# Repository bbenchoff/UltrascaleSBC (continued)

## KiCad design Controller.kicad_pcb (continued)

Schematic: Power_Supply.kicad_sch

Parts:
C42, C51, C53, C129, C130: 1uF; C_0402_1005Metric; MPN CL05A105KA5NQNC; LCSC C52923
C43, C44, C48, C49, C50, C219: 4.7uF; C_0402_1005Metric; MPN CL05A475MP5NRNC; LCSC C23733
C45, C46: 2.2uF; C_0402_1005Metric; MPN CL05A225KO5NQNC; LCSC C170151
C47, C52, C54, C55, C79, C88, C97: 100nF; C_0402_1005Metric; MPN CL05B104KO5NNNC; LCSC C1525
C58, C73: 10uF; C_0402_1005Metric; MPN CL05A106MP5NUNC; LCSC C315248
C59, C60, C61, C62, C63, C64, C65, C66, C67, C68, C69, C70, C71, C72, C74, C75, C80, C81, C82, C83, C84, C85, C89, C90, C91, C92, C93, C94, C98, C99, C100, C101, C217, C218: 22uF; C_0603_1608Metric; MPN CC0603MRX5R5BB226; LCSC C109448
C77, C78, C86, C87, C95, C96, C221: 22uF; C_0805_2012Metric; MPN CGA0805X5R226M250MT; LCSC C6119899
D1, D2: LED; LED_0603_1608Metric; MPN KT-0603G; LCSC C12624
IC1: TPS6508640RSKR; QFN40P800X800X100-65N-D; Mouser Part Number 595-TPS6508640RSKR
J2: Conn_01x03_Pin; JST_VH_B3PS-VH_1x03_P3.96mm_Horizontal; MPN B3PS-VH(LF)(SN); LCSC C131336
L1, L2, L3: 0.47µH; L_Chilisin_BWVS00505020; MPN SMNR5020-R47MT; LCSC C135279
L4, L6: 0.47µH; L_Vishay_IFSC-1515AH_4x4x1.8mm; MPN HTMD-4020-R47-M; LCSC C54321646
L5: 1µH; L_Bourns_SRP7028A_7.3x6.6mm; MPN SRP7028A-1R0M; LCSC C3223644
NT1, NT2, NT3: NetTie_2; NetTie-2_SMD_Pad0.5mm
Q1: BSS138; SOT-23; MPN BSS138; LCSC C7420339
R88, R89, R90, R91, R92, R93, R95, R96, R97, R98, R99, R100, R101: 10kΩ; R_0402_1005Metric; Tolerance 1%; MPN 0402WGF1002TCE; LCSC C25744
R198, R199, R200, R201, R202, R203: 2.2Ω; R_0402_1005Metric; Tolerance 1%; MPN RC0402FR-072R2L; LCSC C327251
R212: 2.2kΩ; R_0805_2012Metric; Tolerance 1%; MPN 0805W8F2201T5E; LCSC C17520
R213: 470Ω; R_0805_2012Metric; Tolerance 1%; MPN 0805W8F4700T5E; LCSC C17710
U23, U24, U25: CSD87381P; CSD87381P_TEX; MPN CSD87381P; LCSC C464808

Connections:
+0V6_VTT: C74.1, C75.1, C217.1, C218.1, IC1.47 (VTT), IC1.48 (VTTFB); also elsewhere on the board
+0V9_BUCK4: C64.1, C65.1, C66.1, C67.1, IC1.23 (FB4), L2.2
+0V85_VCCINT: C80.1, C81.1, C82.1, C83.1, C84.1, C85.1, IC1.2 (FBVOUT2), L4.1; also elsewhere on the board
+1V2_LDOA3: C50.1, IC1.49 (LDOA3)
+1V2_MGTAVTT: C69.1, C70.1, C71.1, C72.1, IC1.12 (FB3), L3.2; also elsewhere on the board
+1V2_VDDQ: C73.1, C98.1, C99.1, C100.1, C101.1, IC1.44 (FBVOUT6), IC1.46 (PVINVTT), L6.1; also elsewhere on the board
+1V5_LDOA2: C49.1, IC1.51 (LDOA2)
+1V8: C53.1, C59.1, C60.1, C61.1, C62.1, C219.1, IC1.18 (PVINSWB1_B2), IC1.22 (FB5), IC1.50 (PVINLDOA2_A3), L1.2; also elsewhere on the board
+1V8_MGTAVCCAUX: C54.1, IC1.17 (SWB1)
+1V8_SWB2: C55.1, IC1.19 (SWB2)
+2V5_VPP: C48.1, IC1.9 (LDOA1); also elsewhere on the board
+3V3: C51.1, C58.1, C63.1, C68.1, C89.1, C90.1, C91.1, C92.1, C93.1, C94.1, IC1.11 (PVIN3), IC1.21 (PVIN5), IC1.24 (PVIN4), IC1.29 (FBVOUT1), IC1.32 (PVINSWA1), L5.1, R213.2; also elsewhere on the board
+3V3_PMIC: C43.1, IC1.54 (LDO3P3), R88.2, R89.1, R90.1, R93.2, R95.2, R96.2, R97.2, R98.2
+3V3_PSIO: C52.1, IC1.31 (SWA1); also elsewhere on the board
+12V: C42.2, C77.1, C78.1, C86.1, C87.1, C95.1, C96.1, C129.2, C130.2, C221.1, IC1.55 (VSYS), J2.1, R212.2, U23.2 (VIN), U24.2 (VIN), U25.2 (VIN); also elsewhere on the board
/Power_Supply/+5_DRV: C44.1, C45.1, C46.1, IC1.8 (DRV5V_2_A1), IC1.38 (DRV5V_1_6), IC1.56 (LDO5P0), IC1.57 (V5ANA)
/Power_Supply/DRVH1: IC1.33 (DRVH1), R201.1
/Power_Supply/DRVH2: IC1.3 (DRVH2), R198.1
/Power_Supply/DRVH6: IC1.43 (DRVH6), R203.1
/Power_Supply/DRVL1: IC1.37 (DRVL1), R200.2
/Power_Supply/DRVL2: IC1.7 (DRVL2), R199.2
/Power_Supply/DRVL6: IC1.39 (DRVL6), R202.2
/Power_Supply/GPO1: IC1.16 (GPO1), IC1.62 (CTL4)
/Power_Supply/PGNDSNS1: IC1.36 (PGNDSNS1), NT2.2
/Power_Supply/PGNDSNS2: IC1.6 (PGNDSNS2), NT1.1
/Power_Supply/PGNDSNS6: IC1.40 (PGNDSNS6), NT3.1
/Power_Supply/SW1: C88.1, IC1.34 (SW1), L5.2, U23.5 (VSW)
/Power_Supply/SW2: C79.1, IC1.4 (SW2), L4.2, U24.5 (VSW)
/Power_Supply/SW6: C97.2, IC1.42 (SW6), L6.2, U25.5 (VSW)
GND: C42.1, C43.2, C44.2, C45.2, C46.2, C47.2, C48.2, C49.2, C50.2, C51.2, C52.2, C53.2, C54.2, C55.2, C58.2, C59.2, C60.2, C61.2, C62.2, C63.2, C64.2, C65.2, C66.2, C67.2, C68.2, C69.2, C70.2, C71.2, C72.2, C73.2, C74.2, C75.2, C77.2, C78.2, C80.2, C81.2, C82.2, C83.2, C84.2, C85.2, C86.2, C87.2, C89.2, C90.2, C91.2, C92.2, C93.2, C94.2, C95.2, C96.2, C98.2, C99.2, C100.2, C101.2, C129.1, C130.1, C217.2, C218.2, C219.2, C221.2, D1.1 (K), IC1.1 (FBGND2), IC1.52 (AGND), IC1.65 (EP), J2.3, NT1.2, NT2.1, NT3.2, Q1.2 (S), R91.1, R92.1, R99.2, R100.2, R101.2, U23.3 (PGND), U24.3 (PGND), U25.3 (PGND); also elsewhere on the board
unnamed: D1.2 (A), R212.1
unnamed: D2.2 (A), R213.1
unnamed: D2.1 (K), Q1.3 (D)
unnamed: C88.2, IC1.35 (BOOT1)
unnamed: C79.2, IC1.5 (BOOT2)
unnamed: C97.1, IC1.41 (BOOT6)
unnamed: IC1.13 (CTL1), R88.1
unnamed: IC1.60 (CTL2), R91.2
unnamed: IC1.61 (CTL3/SLPENB1), R89.2
unnamed: IC1.63 (CTL5), R90.2
unnamed: IC1.14 (CTL6/SLPENB2), R92.2
unnamed: IC1.26 (GPO2), R93.1
unnamed: IC1.28 (GPO4), R95.1
unnamed: IC1.30 (ILIM1), R100.1
unnamed: IC1.64 (ILIM2), R99.1
unnamed: IC1.45 (ILIM6), R101.1
unnamed: IC1.10 (LX3), L3.1
unnamed: IC1.25 (LX4), L2.1
unnamed: IC1.20 (LX5), L1.1
unnamed: C47.1, IC1.53 (VREF)
unnamed: R200.1, U23.4 (BG)
unnamed: R201.2, U23.1 (TG)
unnamed: R199.1, U24.4 (BG)
unnamed: R198.2, U24.1 (TG)
unnamed: R202.1, U25.4 (BG)
unnamed: R203.2, U25.1 (TG)
PMIC_IRQ: IC1.15 (IRQB), R98.1; also elsewhere on the board
PMIC_SCL: IC1.58 (CLK), R96.1; also elsewhere on the board
PMIC_SDA: IC1.59 (DATA), R97.1; also elsewhere on the board
PS_POR_B: IC1.27 (GPO3), Q1.1 (G); also elsewhere on the board

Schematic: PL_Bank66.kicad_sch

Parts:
U1: XCZU3EG-2SFVC784I; SFVC784_AMD; MPN XCZU3EG-2SFVC784I; LCSC C1550463

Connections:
+1V8: U1.B7 (VCCO_66), U1.D3 (VCCO_66), U1.E6 (VCCO_66); also elsewhere on the board
EXP_IO18_0: U1.A2 (IO_L8P_T1L_N2_AD5P_66); also elsewhere on the board
EXP_IO18_1: U1.D2 (IO_T1U_N12_66); also elsewhere on the board
EXP_IO18_2: U1.C7 (IO_T3U_N12_66); also elsewhere on the board
EXP_P0_N: U1.C2 (IO_L12N_T1U_N11_GC_66); also elsewhere on the board
EXP_P0_P: U1.C3 (IO_L12P_T1U_N10_GC_66); also elsewhere on the board
EXP_P1_N: U1.F1 (IO_L1N_T0L_N1_DBC_66); also elsewhere on the board
EXP_P1_P: U1.G1 (IO_L1P_T0L_N0_DBC_66); also elsewhere on the board
EXP_P2_N: U1.D1 (IO_L2N_T0L_N3_66); also elsewhere on the board
EXP_P2_P: U1.E1 (IO_L2P_T0L_N2_66); also elsewhere on the board
EXP_P3_N: U1.A6 (IO_L21N_T3L_N5_AD8N_66); also elsewhere on the board
EXP_P3_P: U1.A7 (IO_L21P_T3L_N4_AD8P_66); also elsewhere on the board
EXP_P4_N: U1.A8 (IO_L23N_T3U_N9_66); also elsewhere on the board
EXP_P4_P: U1.A9 (IO_L23P_T3U_N8_66); also elsewhere on the board
EXP_P6_N: U1.B1 (IO_L7N_T1L_N1_QBC_AD13N_66); also elsewhere on the board
EXP_P6_P: U1.C1 (IO_L7P_T1L_N0_QBC_AD13P_66); also elsewhere on the board
EXP_P7_N: U1.A4 (IO_L10N_T1U_N7_QBC_AD4N_66); also elsewhere on the board
EXP_P7_P: U1.B4 (IO_L10P_T1U_N6_QBC_AD4P_66); also elsewhere on the board
EXP_P8_N: U1.A5 (IO_L19N_T3L_N1_DBC_AD9N_66); also elsewhere on the board
EXP_P8_P: U1.B5 (IO_L19P_T3L_N0_DBC_AD9P_66); also elsewhere on the board
EXP_P9_N: U1.E2 (IO_L3N_T0L_N5_AD15N_66); also elsewhere on the board
EXP_P9_P: U1.F2 (IO_L3P_T0L_N4_AD15P_66); also elsewhere on the board
EXP_P10_N: U1.C4 (IO_L11N_T1U_N9_GC_66); also elsewhere on the board
EXP_P10_P: U1.D4 (IO_L11P_T1U_N8_GC_66); also elsewhere on the board
EXP_P11_N: U1.A3 (IO_L9N_T1L_N5_AD12N_66); also elsewhere on the board
EXP_P11_P: U1.B3 (IO_L9P_T1L_N4_AD12P_66); also elsewhere on the board
EXP_P12_N: U1.B6 (IO_L20N_T3L_N3_AD1N_66); also elsewhere on the board
EXP_P12_P: U1.C6 (IO_L20P_T3L_N2_AD1P_66); also elsewhere on the board
EXP_P13_N: U1.B8 (IO_L22N_T3U_N7_DBC_AD0N_66); also elsewhere on the board
EXP_P13_P: U1.C8 (IO_L22P_T3U_N6_DBC_AD0P_66); also elsewhere on the board
EXP_P14_N: U1.B9 (IO_L24N_T3U_N11_66); also elsewhere on the board
EXP_P16_P: U1.G3 (IO_L4P_T0U_N6_DBC_AD7P_66); also elsewhere on the board
EXP_P17_N: U1.E3 (IO_L5N_T0U_N9_AD14N_66); also elsewhere on the board
EXP_P17_P: U1.E4 (IO_L5P_T0U_N8_AD14P_66); also elsewhere on the board
GND: U1.G9 (VREF_66); also elsewhere on the board
HSFAN_TACH: U1.A1 (IO_L8N_T1L_N3_AD5N_66); also elsewhere on the board

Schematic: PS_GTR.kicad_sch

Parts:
C1, C2, C5, C6, C7, C8, C56, C167, C168, C169, C170, C171, C172, C173, C174, C175, C176, C177, C192, C193, C194, C195, C196, C210, C211, C212, C213, C231, C232, C329, C331: 100nF; C_0402_1005Metric; MPN CL05B104KO5NNNC; LCSC C1525
C14, C15: 27pF; C_0402_1005Metric; MPN 0402CG270J500NT; LCSC C1557
C16, C17: 18pF; C_0402_1005Metric; MPN 0402CG180J500NT; LCSC C1549
C19, C28, C29, C226, C227, C228, C229, C230: 100 nF, ±10%, 16 V, X5R; C_0201_0603Metric; MPN CL03A104KO3NNNC; LCSC C307380
C127, C128: 10nF; C_0402_1005Metric; MPN CL05B103KB5NNNC; LCSC C15195
C137, C207, C208, C209: 150uF; CP_EIA-3528-21_Kemet-B; MPN T520B157M006ATE035; LCSC C212682
C164, C166, C340: 10uF; C_0402_1005Metric; MPN CL05A106MP5NUNC; LCSC C315248
C165: 47nF; C_0402_1005Metric; MPN TCC0402X7R473K500AT; LCSC C880605
C222, C223, C338: 4.7uF; C_0402_1005Metric; MPN CL05A475MP5NRNC; LCSC C23733
C224: 2.2uF; C_0402_1005Metric; MPN CL05A225MQ5NSNC; LCSC C12530
C332, C333, C339: 1uF; C_0402_1005Metric; MPN CL05A105KA5NQNC; LCSC C52923
C334, C335, C336, C337: 1nF; C_0402_1005Metric; MPN 0402B102K500NT; LCSC C1523
FB1: FerriteBead; L_0805_2012Metric; MPN BLM21AG601SH1D; LCSC C437406
H7: 9774025243R; Spacer_M2_H2.5mm_9774025243R; Part Number 9774025243R
J4, J12: USB3_A_Stacked; USB3_A_Molex_48406-0001_Horizontal_Stacked; MPN HC-USB3.0-L175-2X1-P; LCSC C7501881
J5: 47272-0001; 472720001; Mouser Part Number 538-47272-0001
J11: 1-2199119-5; MDT275; MPN 1-2199119-5; LCSC C574849
R38, R108, R116: 100kΩ; R_0402_1005Metric; Tolerance 1%; MPN 0402WGF1003TCE; LCSC C25741
R39, R104: 49.9Ω; R_0402_1005Metric; Tolerance 1%; MPN 0402WGF499JTCE; LCSC C25120
R57: 1MΩ; R_0402_1005Metric; MPN 0402WGF1004TCE; LCSC C26083
R64, R115, R248, R253: 10kΩ; R_0402_1005Metric; MPN 0402WGF1002TCE; LCSC C25744
R65: 12kΩ; R_0402_1005Metric; MPN 0402WGF1202TCE; LCSC C25752
R66: 8.06kΩ; R_0402_1005Metric; MPN 0402WGF8061TCE; LCSC C25923
R67: 2.49kΩ; R_0402_1005Metric; Tolerance 1%; MPN 0402WGF2491TCE; LCSC C25884
R68, R69, R70, R113, R114: 10kΩ; R_0402_1005Metric; Tolerance 1%; MPN 0402WGF1002TCE; LCSC C25744
R80: 4.99kΩ; R_0402_1005Metric; Tolerance 1%; MPN 0402WGF4991TCE; LCSC C25903
R94: 1.5kΩ; R_0402_1005Metric; Tolerance 1%; MPN 0402WGF1501TCE; LCSC C25867
R231, R232, R249: 0Ω; R_0402_1005Metric; MPN 0402WGF0000TCE; LCSC C17168
R233, R234: 49.9Ω; R_0402_1005Metric; MPN 0402WGF499JTCE; LCSC C25120
R250, R251: 200kΩ; R_0402_1005Metric; MPN 0402WGF2003TCE; LCSC C25764
R252: 619Ω; R_0402_1005Metric; MPN 0402WGF6190TCE; LCSC C473032
TP1, TP2, TP3: TestPoint; TestPoint_Pad_D1.0mm
U1: XCZU3EG-2SFVC784I; SFVC784_AMD; MPN XCZU3EG-2SFVC784I; LCSC C1550463
U5: USB5744-I/2G; QFN-56-1EP_7x7mm_P0.4mm_EP4.6x4.6mm_ThermalVias; MPN USB5744-I/2G; LCSC C633621
U6: USB3320C-EZK-TR; QFN-32-1EP_5x5mm_P0.5mm_EP3.3x3.3mm_ThermalVias; MPN USB3320C-EZK-TR; LCSC C132156
U22, U46: TPS74801DRC; VSON-10-1EP_3x3mm_P0.5mm_EP1.65x2.4mm_ThermalVias; MPN TPS74801DRCR; LCSC C105263
U26: FIN1019MTC; TSSOP-14_4.4x5mm_P0.65mm; MPN FIN1019MTCX; LCSC C903667
U40, U41, U42, U43: AP2171WG-7; SOT-23-5; MPN AP2171WG-7; LCSC C110466
U45: AP2112K-1.8TRG1; SOT-23-5; MPN AP2112K-1.8TRG1; LCSC C176944
Y3: DSC1124CI1-027.0000T; DSC1124_3225; MPN DSC1124CI1-027.0000T; LCSC C1995498
Y4: TX322524M4LBDD2T; Crystal_SMD_3225-4Pin_3.2x2.5mm; MPN TX322524M4LBDD2T; LCSC C5308006
Y5: X1E000021064800; Crystal_SMD_3225-4Pin_3.2x2.5mm; MPN X1E000021064800; LCSC C25832917

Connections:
+0V85_MGTRAVCC: C340.1, R252.1, U46.9 (OUT), U46.10 (OUT); also elsewhere on the board
+1V2_USB: C166.1, C167.2, C168.2, C169.2, C170.2, C171.2, C172.2, C173.2, C174.2, C334.1, C335.1, R80.2, U5.5 (VDD12), U5.12 (VDD12), U5.15 (VDD12), U5.21 (VDD12), U5.28 (VDD12), U5.33 (VDD12), U5.43 (VDD12), U5.49 (VDD12), U22.9 (OUT), U22.10 (OUT)
+1V8: C338.1, U46.1 (IN), U46.2 (IN), U46.5 (EN); also elsewhere on the board
+1V8_USB: C195.1, C196.1, C222.1, C223.1, C333.1, U6.28 (VDD18), U6.30 (VDD18), U45.5 (VOUT)
+3V3: C56.2, C164.1, C175.2, C176.2, C177.2, C192.2, C193.2, C194.2, C329.1, C332.1, C336.1, C337.1, C339.1, FB1.2, R64.1, R67.1, R114.2, R116.1, R248.1, R251.1, U5.16 (VDD33), U5.31 (VDD33), U5.37 (VBUS_DET), U5.44 (VDD33), U5.55 (VDD33), U6.8 (REFSEL0), U6.11 (REFSEL1), U6.14 (REFSEL2), U6.32 (VDDIO), U22.1 (IN), U22.2 (IN), U22.4 (BIAS), U22.5 (EN), U26.14 (VCC), U45.1 (VIN), U45.3 (EN), U46.4 (BIAS), Y3.1 (OE), Y3.6 (VDD); also elsewhere on the board
+3V3_NVMe: J11.2 (+3.3V), J11.4 (+3.3V), J11.12 (+3.3V), J11.14 (+3.3V), J11.16 (+3.3V), J11.18 (+3.3V), J11.70 (+3.3V), J11.72 (+3.3V), J11.74 (+3.3V), R68.2, R69.2, R70.2; also elsewhere on the board
+5V_USB: C331.1, R115.1, U6.21 (VBAT), U40.5 (IN), U41.5 (IN), U42.5 (IN), U43.5 (IN); also elsewhere on the board
/PS_GTR/27MHZ_REFCLK+: C127.2, U1.F23 (PS_MGTREFCLK0P_505)
/PS_GTR/27MHZ_REFCLK-: C128.2, U1.F24 (PS_MGTREFCLK0N_505)
/PS_GTR/+5_PORT1: C137.1, J4.1 (VBUS1), U40.1 (OUT)
/PS_GTR/+5_PORT2: C207.1, J4.10 (VBUS2), U41.1 (OUT)
/PS_GTR/+5_PORT3: C208.1, J12.1 (VBUS1), U42.1 (OUT)
/PS_GTR/+5_PORT4: C209.1, J12.10 (VBUS2), U43.1 (OUT)
/PS_GTR/DP_AUX_CONN_N: C232.2, J5.17 (AUX_CH-), R116.2
/PS_GTR/DP_AUX_CONN_P: C231.2, J5.15 (AUX_CH+), R108.2
/PS_GTR/FPGA_REFCLK_N: U1.E22 (PS_MGTREFCLK1N_505); also elsewhere on the board
/PS_GTR/FPGA_REFCLK_P: U1.E21 (PS_MGTREFCLK1P_505); also elsewhere on the board
/PS_GTR/M2_REFCLK_N: J11.53 (REFCLKn); also elsewhere on the board
/PS_GTR/M2_REFCLK_P: J11.55 (REFCLKp); also elsewhere on the board
/PS_GTR/MGTRAVCC_FB: R252.2, R253.1, U46.8 (FB)
/PS_GTR/ML_Lane0+: C5.2, J5.1 (ML_Lane0+)
/PS_GTR/ML_Lane0-: C6.2, J5.3 (ML_Lane0-)
/PS_GTR/ML_Lane1+: C7.2, J5.4 (ML_Lane1+)
/PS_GTR/ML_Lane1-: C8.2, J5.6 (ML_Lane1-)
/PS_GTR/PCIE_RX+: J11.43 (PERp0), U1.F27 (PS_MGTRRXP0_505)
/PS_GTR/PCIE_RX-: J11.41 (PERn0), U1.F28 (PS_MGTRRXN0_505)
/PS_GTR/PCIE_TX+: C1.2, J11.49 (PETp0)
/PS_GTR/PCIE_TX-: C2.2, J11.47 (PETn0)
/PS_GTR/U22_PowerGood: R114.1, U22.3 (PG)
/PS_GTR/USB1_D1+: J4.3 (D1+), U5.1 (USB2DN_DP1/PRT_DIS_P1)
/PS_GTR/USB1_D1-: J4.2 (D1-), U5.2 (USB2DN_DM1/PRT_DIS_M1)
/PS_GTR/USB1_PRT_CTL: U5.36 (PRT_CTL1), U40.3 (~FLG), U40.4 (EN)
/PS_GTR/USB1_SSRX1+: J4.6 (SSRX1+), U5.6 (USB3DN_RXDP1)
/PS_GTR/USB1_SSRX1-: J4.5 (SSRX1-), U5.7 (USB3DN_RXDM1)
/PS_GTR/USB1_SSTX1+: C28.1, U5.3 (USB3DN_TXDP1)
/PS_GTR/USB1_SSTX1-: C19.1, U5.4 (USB3DN_TXDM1)
/PS_GTR/USB1_TX+: C28.2, J4.9 (SSTX1+)
/PS_GTR/USB1_TX-: C19.2, J4.8 (SSTX1-)
/PS_GTR/USB2_D2+: J4.12 (D2+), U5.8 (USB2DN_DP2/PRT_DIS_P2)
/PS_GTR/USB2_D2-: J4.11 (D2-), U5.9 (USB2DN_DM2/PRT_DIS_M2)
/PS_GTR/USB2_PRT_CTL: U5.35 (PRT_CTL2), U41.3 (~FLG), U41.4 (EN)
/PS_GTR/USB2_SSRX2+: J4.15 (SSRX2+), U5.13 (USB3DN_RXDP2)
/PS_GTR/USB2_SSRX2-: J4.14 (SSRX2-), U5.14 (USB3DN_RXDM2)
/PS_GTR/USB2_SSTX2+: C226.1, U5.10 (USB3DN_TXDP2)
/PS_GTR/USB2_SSTX2-: C29.1, U5.11 (USB3DN_TXDM2)
/PS_GTR/USB2_TX+: C226.2, J4.18 (SSTX2+)
/PS_GTR/USB2_TX-: C29.2, J4.17 (SSTX2-)
/PS_GTR/USB3_D1+: J12.3 (D1+), U5.17 (USB2DN_DP3/PRT_DIS_P3)
/PS_GTR/USB3_D1-: J12.2 (D1-), U5.18 (USB2DN_DM3/PRT_DIS_M3)
/PS_GTR/USB3_PRT_CTL: U5.34 (PRT_CTL3), U42.3 (~FLG), U42.4 (EN)
/PS_GTR/USB3_SSRX1+: J12.6 (SSRX1+), U5.22 (USB3DN_RXDP3)
/PS_GTR/USB3_SSRX1-: J12.5 (SSRX1-), U5.23 (USB3DN_RXDM3)
/PS_GTR/USB3_SSTX1+: C228.1, U5.19 (USB3DN_TXDP3)
/PS_GTR/USB3_SSTX1-: C227.1, U5.20 (USB3DN_TXDM3)
/PS_GTR/USB3_TX+: C228.2, J12.9 (SSTX1+)
/PS_GTR/USB3_TX-: C227.2, J12.8 (SSTX1-)
/PS_GTR/USB4_D2+: J12.12 (D2+), U5.24 (USB2DN_DP4/PRT_DIS_P4)
/PS_GTR/USB4_D2-: J12.11 (D2-), U5.25 (USB2DN_DM4/PRT_DIS_M4)
/PS_GTR/USB4_PRT_CTL: U5.32 (PRT_CTL4/GANG_PWR), U43.3 (~FLG), U43.4 (EN)
/PS_GTR/USB4_SSRX2+: J12.15 (SSRX2+), U5.29 (USB3DN_RXDP4)
/PS_GTR/USB4_SSRX2-: J12.14 (SSRX2-), U5.30 (USB3DN_RXDM4)
/PS_GTR/USB4_SSTX2+: C230.1, U5.26 (USB3DN_TXDP4)
/PS_GTR/USB4_SSTX2-: C229.1, U5.27 (USB3DN_TXDM4)
/PS_GTR/USB4_TX+: C230.2, J12.18 (SSTX2+)
/PS_GTR/USB4_TX-: C229.2, J12.17 (SSTX2-)
/PS_GTR/USB_D+: TP1.1 (1_1), U5.45 (USB2UP_DP), U6.18 (DP)
/PS_GTR/USB_D-: TP2.1 (1_1), U5.46 (USB2UP_DM), U6.19 (DM)
/PS_GTR/USB_HUB_ATEST: R249.1, U5.52 (ATEST)
/PS_GTR/USB_HUB_CFG_BC_EN: R250.1, U5.40 (SPI_DI/CFG_BC_EN)
/PS_GTR/USB_HUB_CFG_NON_REM: R251.2, U5.41 (SPI_CE_N/CFG_NON_REM)
/PS_GTR/USB_HUB_RBIAS: R65.1, U5.56 (RBIAS)
/PS_GTR/USB_HUB_XI: C14.1, U5.54 (XTALI/CLK_IN), Y5.1
/PS_GTR/USB_HUB_XO: C15.1, U5.53 (XTALO), Y5.3
/PS_GTR/USB_PHY_RBIAS: R66.1, U6.24 (RBIAS)
/PS_GTR/USB_PHY_VBUS: R115.2, U6.22 (VBUS)
/PS_GTR/USB_PHY_VDD33: C224.1, U6.20 (VDD33)
/PS_GTR/USB_PHY_XI: C17.1, R57.1, U6.26 (REFCLK), Y4.1
/PS_GTR/USB_PHY_XO: C16.1, R57.2, U6.25 (XO), Y4.3
/PS_GTR/USB_SSRX+: C213.2, U5.50 (USB3UP_RXDP)
/PS_GTR/USB_SSRX-: C212.2, U5.51 (USB3UP_RXDM)
/PS_GTR/USB_SSTX+: C210.2, U5.47 (USB3UP_TXDP)
/PS_GTR/USB_SSTX-: C211.2, U5.48 (USB3UP_TXDM)
/PS_GTR/Z_ML_LANE1+: C7.1, U1.C25 (PS_MGTRTXP2_505)
/PS_GTR/Z_ML_LANE1-: C8.1, U1.C26 (PS_MGTRTXN2_505)
/PS_GTR/Z_ML_Lane0+: C5.1, U1.B23 (PS_MGTRTXP3_505)
/PS_GTR/Z_ML_Lane0-: C6.1, U1.B24 (PS_MGTRTXN3_505)
/PS_GTR/Z_PCIE_TX+: C1.1, U1.E25 (PS_MGTRTXP0_505)
/PS_GTR/Z_PCIE_TX-: C2.1, U1.E26 (PS_MGTRTXN0_505)
/PS_GTR/Z_USB_SSRX+: C213.1, U1.D23 (PS_MGTRTXP1_505)
/PS_GTR/Z_USB_SSRX-: C212.1, U1.D24 (PS_MGTRTXN1_505)
/PS_GTR/Z_USB_SSTX+: C210.1, U1.D27 (PS_MGTRRXP1_505)
/PS_GTR/Z_USB_SSTX-: C211.1, U1.D28 (PS_MGTRRXN1_505)
DP_AUX_BIAS: R39.1, R67.2, R94.1, R104.1
DP_AUX_CH+: C231.1, R39.2, U26.10 (RI+), U26.12 (DO+)
DP_AUX_CH-: C232.1, R104.2, U26.9 (RI-), U26.11 (DO-)
DP_HPD: J5.18 (HPD), R38.2; also elsewhere on the board
DP_PS_MIO27: U26.2 (DI); also elsewhere on the board
DP_PS_MIO29: U26.1 (DE), U26.8 (~RE); also elsewhere on the board
DP_PS_MIO30: U26.4 (RO); also elsewhere on the board
GND: C14.2, C15.2, C16.2, C17.2, C56.1, C137.2, C164.2, C165.1, C166.2, C167.1, C168.1, C169.1, C170.1, C171.1, C172.1, C173.1, C174.1, C175.1, C176.1, C177.1, C192.1, C193.1, C194.1, C195.2, C196.2, C207.2, C208.2, C209.2, C222.2, C223.2, C224.2, C329.2, C331.2, C332.2, C333.2, C334.2, C335.2, C336.2, C337.2, C338.2, C339.2, C340.2, J4.4 (GND1), J4.7 (DRAIN1), J4.13 (GND2), J4.16 (DRAIN2), J4.19 (SHIELD), J5.2 (GND), J5.5 (GND), J5.8 (GND), J5.11 (GND), J5.13 (CONFIG1), J5.14 (CONFIG2), J5.16 (GND), J5.19 (DP_PWR_GND), J5.SH (SHIELD), J11.1 (GND), J11.3 (GND), J11.9 (GND), J11.15 (GND), J11.21 (GND), J11.27 (GND), J11.33 (GND), J11.39 (GND), J11.45 (GND), J11.51 (GND), J11.57 (GND), J11.71 (GND), J11.73 (GND), J11.75 (GND), J12.4 (GND1), J12.7 (DRAIN1), J12.13 (GND2), J12.16 (DRAIN2), J12.19 (SHIELD), R38.1, R65.2, R66.2, R94.2, R108.1, R113.1, R233.2, R234.2, R249.2, R250.2, R253.2, TP3.1 (1_1), U5.57 (GND_PAD), U6.23 (ID), U6.33 (CTR_GND), U22.6 (GND), U22.11 (GND), U26.7 (GND), U40.2 (GND), U41.2 (GND), U42.2 (GND), U43.2 (GND), U45.2 (GND), U46.6 (GND), U46.11 (GND), Y3.3 (GND), Y4.2 (G), Y4.4 (G), Y5.2 (G), Y5.4 (G); also elsewhere on the board
I2C0_SCL: U5.38 (SPI_CLK/SMCLK); also elsewhere on the board
I2C0_SDA: U5.39 (SPI_DO/SMDAT); also elsewhere on the board
M2_PERST#: J11.50 (PERST#); also elsewhere on the board
unnamed: C127.1, R231.2, R233.1
unnamed: C128.1, R232.2, R234.1
unnamed: FB1.1, J5.20 (DP_PWR)
unnamed: J11.52 (CLKREQ#), R68.1
unnamed: J11.69 (PEDET), R70.1
unnamed: J11.54 (PEWAKE#), R69.1
unnamed: R80.1, R113.2, U22.8 (FB)
unnamed: C165.2, U22.7 (SS)
unnamed: R231.1, Y3.4 (OUT+)
unnamed: R232.1, Y3.5 (OUT-)
USB_CLKOUT: U6.1 (CLKOUT); also elsewhere on the board
USB_DATA0: U6.3 (DATA0); also elsewhere on the board
USB_DATA1: U6.4 (DATA1); also elsewhere on the board
USB_DATA2: U6.5 (DATA2); also elsewhere on the board
USB_DATA3: U6.6 (DATA3); also elsewhere on the board
USB_DATA4: U6.7 (DATA4); also elsewhere on the board
USB_DATA5: U6.9 (DATA5); also elsewhere on the board
USB_DATA6: U6.10 (DATA6); also elsewhere on the board
USB_DATA7: U6.13 (DATA7); also elsewhere on the board
USB_DIR: U6.31 (DIR); also elsewhere on the board
USB_HUB_RESET_B: R64.2, U5.42 (RESET_N); also elsewhere on the board
USB_NXT: U6.2 (NXT); also elsewhere on the board
USB_PHY_RESET_B: R248.2, U6.27 (RESETB); also elsewhere on the board
USB_STP: U6.29 (STP); also elsewhere on the board

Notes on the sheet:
U46: PS_MGTRAVCC 0.85 V LDO (Rev C item 9). PMIC BUCK4 (0.90 V OTP, above the 0.876 V max) no longer feeds PS_MGTRAVCC; it runs unloaded as +0V9_BUCK4. Vout = 0.8 V x (1 + 619/10k) = 0.8495 V. VIN +1V8 (DS925 FPD step 2 with VCC_PSDDR_PLL), BIAS +3V3. UG583: < 10 mVpp noise, dedicated rail, 10 uF a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
USB2 upstream HS probe points (Rev B D10/D13). TP3 = GND for the probe ground spring; place TP1-TP3 within a few mm of U5 pins 45/46.
Rev C USB (2026-11-14): copy of AMD Kria KR260 carrier sheet 24 (USB0 PHY and hub), docs/reference/kr260. Deviations: VDDIO 3.3 V (MIO bank 502), all four downstream ports enabled (no PRT_DIS straps), hub SMBus on I2C0 (RTC bus), AP2171W (1 A) per port (EN+FLG tied to PRT_CTLn, combined mode) inste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
HCSL: R231/R232 initially 0R (DS20005870B Fig. 5-1). 49.9R shunts precede the existing 10nF AC coupling.

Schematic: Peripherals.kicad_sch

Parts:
BT1: CR1220; BatteryHolder_MYOUNG_MY-1220-03_1x1220; MPN MY-1220-03-R; LCSC C964819
C30, C32, C33, C34: 1uF; C_1206_3216Metric; MPN CL31B105KBHNNNE; LCSC C1848
C31: 2.2uF; C_1206_3216Metric; MPN CL31B225KBHNNNE; LCSC C50254
C35, C36, C38, C40, C41: 0.1uF; C_0603_1608Metric; MPN CC0603KRX7R9BB104; LCSC C14663
C37, C39, C216: 10uF; C_1206_3216Metric; MPN CL31A106KBHNNNE; LCSC C13585
FB6: FerriteBead; L_0805_2012Metric; MPN BLM21AG601SH1D; LCSC C437406
J7, J8, J9, J10: Conn_01x04_Pin; FanPinHeader_1x04_P2.54mm_Vertical; MPN 470531000; LCSC C240840
J16: Conn_01x02_Pin; JST_PH_S2B-PH-K_1x02_P2.00mm_Horizontal; MPN S2B-PH-K-S(LF)(SN); LCSC C173752
J17: AudioJack3_SwitchTR; Jack_3.5mm_CUI_SJ1-3535NG_Horizontal; MPN SJ1-3535NG; LCSC C4991610
J18: SZ05S_FAN; Molex_KK-254_AE-6410-03A_1x03_P2.54mm_Vertical; MPN 22272031; LCSC C471416
LS1: Speaker; PUI Audio AS03604AR; MPN AS03604AR
Q2, Q3, Q4, Q5: BSS138; SOT-23; MPN BSS138; LCSC C7420339
R84, R85: 470Ω; R_0402_1005Metric; Tolerance 1%; MPN 0402WGF4700TCE; LCSC C25117
R86, R87: 1kΩ; R_0402_1005Metric; Tolerance 1%; MPN 0402WGF1001TCE; LCSC C11702
R216, R217: 10kΩ; R_0402_1005Metric; Tolerance 1%; MPN 0402WGF1002TCE; LCSC C25744
R235, R236, R237, R239, R240, R242, R243, R245, R246: 10kΩ; R_0402_1005Metric; MPN 0402WGF1002TCE; LCSC C25744
R238, R241, R244, R247: 1kΩ; R_0402_1005Metric; MPN 0402WGF1001TCE; LCSC C11702
U9: PCM5102A; TSSOP-20_4.4x6.5mm_P0.65mm; MPN PCM5102APWR; LCSC C107671
U10: PAM8302AASCR; MSOP-8_3x3mm_P0.65mm; MPN PAM8302AASCR; LCSC C113367
U12: AMS1117-3.3; SOT-223-3_TabPin2; MPN AMS1117-3.3; LCSC C6186
U13: DS3231M; SOIC-16W_7.5x10.3mm_P1.27mm; MPN DS3231M+TRL; LCSC C37663

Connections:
+1V8: R235.1; also elsewhere on the board
+3.3VAudio: C30.1, C35.1, C36.1, C37.1, C38.2, U9.1 (CPVDD), U9.8 (AVDD), U9.17 (XSMT), U9.20 (DVDD), U10.1 (~SD), U12.2 (VO)
+3V3: C41.1, R216.2, R217.1, R237.1, R240.1, R243.1, R246.1, U13.2 (VCC); also elsewhere on the board
+5V_USB: FB6.1, J18.2; also elsewhere on the board
+5_Audio: C34.1, C39.1, C216.2, FB6.2, U10.6 (VDD), U12.3 (VI)
+12V: J7.2, J8.2, J9.2, J10.2; also elsewhere on the board
/Peripherals/Fan1PWM_C: J7.4, Q2.3 (D)
/Peripherals/Fan1Tach_C: J7.3, R237.2, R238.1
/Peripherals/Fan2PWM_C: J8.4, Q3.3 (D)
/Peripherals/Fan2Tach_C: J8.3, R240.2, R241.1
/Peripherals/Fan3PWM_C: J9.4, Q4.3 (D)
/Peripherals/Fan3Tach_C: J9.3, R243.2, R244.1
/Peripherals/Fan4PWM_C: J10.4, Q5.3 (D)
/Peripherals/Fan4Tach_C: J10.3, R246.2, R247.1
/Peripherals/TRS_Ring: J17.R, R85.1
/Peripherals/TRS_Tip: J17.T, R84.2
Fan1PWM: Q2.1 (G), R236.1; also elsewhere on the board
Fan1Tach: R238.2; also elsewhere on the board
Fan2PWM: Q3.1 (G), R239.1; also elsewhere on the board
Fan2Tach: R241.2; also elsewhere on the board
Fan3PWM: Q4.1 (G), R242.1; also elsewhere on the board
Fan3Tach: R244.2; also elsewhere on the board
Fan4PWM: Q5.1 (G), R245.1; also elsewhere on the board
Fan4Tach: R247.2; also elsewhere on the board
GND: BT1.2 (-), C30.2, C32.2, C33.2, C34.2, C35.2, C36.2, C37.2, C38.1, C39.2, C40.2, C41.2, C216.1, J7.1, J8.1, J9.1, J10.1, J17.S, J18.1, Q2.2 (S), Q3.2 (S), Q4.2 (S), Q5.2 (S), R236.2, R239.2, R242.2, R245.2, U9.3 (CPGND), U9.9 (AGND), U9.10 (DEMP), U9.11 (FLT), U9.12 (SCK), U9.16 (FMT), U9.19 (DGND), U10.7 (GND), U12.1 (GND), U13.5 (GND), U13.6 (GND), U13.7 (GND), U13.8 (GND), U13.9 (GND), U13.10 (GND), U13.11 (GND), U13.12 (GND), U13.13 (GND); also elsewhere on the board
HSFAN_TACH: J18.3, R235.2; also elsewhere on the board
I2C0_SCL: R216.1, U13.16 (SCL); also elsewhere on the board
I2C0_SDA: R217.2, U13.15 (SDA); also elsewhere on the board
I2S_BCK: U9.13 (BCK); also elsewhere on the board
I2S_DIN: U9.14 (DIN); also elsewhere on the board
I2S_LRCK: U9.15 (LRCK); also elsewhere on the board
unnamed: BT1.1 (+), U13.14 (VBAT)
unnamed: J16.1, LS1.2, U10.8 (OUT-)
unnamed: J16.2, LS1.1, U10.5 (OUT+)
unnamed: J17.RN, R86.1
unnamed: J17.TN, R87.1
unnamed: C31.2, U9.4 (CAPM)
unnamed: C31.1, U9.2 (CAPP)
unnamed: C32.1, U9.18 (LDOO)
unnamed: R84.1, U9.6 (OUTL)
unnamed: R85.2, U9.7 (OUTR)
unnamed: C33.1, U9.5 (VNEG)
unnamed: R86.2, R87.2, U10.3 (IN+)
unnamed: C40.1, U10.4 (IN-)

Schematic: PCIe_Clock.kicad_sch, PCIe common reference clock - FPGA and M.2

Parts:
C3, C4, C326, C327: 10nF; C_0402_1005Metric; MPN CL05B103KB5NNNC; LCSC C15195
C324, C325: 20pF; C_0402_1005Metric; MPN 0402CG200J500NT; LCSC C1554
C328: 1uF; C_0402_1005Metric; MPN CL05A105KA5NQNC; LCSC C52923
R222: 475; R_0402_1005Metric; MPN RC0402FR-07475RL; LCSC C137975
R223, R225, R227, R229: 33; R_0402_1005Metric; MPN 0402WGF330JTCE; LCSC C25105
R224, R226, R228, R230: 49.9Ω; R_0402_1005Metric; MPN 0402WGF499JTCE; LCSC C25120
U44: PI6C557-03BLEX; PI6C557-03B_TSSOP16; MPN PI6C557-03BLEX; LCSC C1540638
Y1: 25MHz; YXC_YSX321SL_3225; MPN X322525MRB4SI; LCSC C70593

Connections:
+3V3: C326.1, C327.1, C328.1, U44.1 (S0), U44.6 (OE), U44.12 (VDDA), U44.16 (VDDX); also elsewhere on the board
/PS_GTR/FPGA_REFCLK_N: C3.2; also elsewhere on the board
/PS_GTR/FPGA_REFCLK_P: C4.2; also elsewhere on the board
/PS_GTR/M2_REFCLK_N: R229.2, R230.1; also elsewhere on the board
/PS_GTR/M2_REFCLK_P: R227.2, R228.1; also elsewhere on the board
/PS_GTR/PCIe_Clock/CLK0_N: R225.1, U44.14 (CLK0_N)
/PS_GTR/PCIe_Clock/CLK0_P: R223.1, U44.15 (CLK0_P)
/PS_GTR/PCIe_Clock/CLK1_N: R229.1, U44.10 (CLK1_N)
/PS_GTR/PCIe_Clock/CLK1_P: R227.1, U44.11 (CLK1_P)
/PS_GTR/PCIe_Clock/IREF: R222.1, U44.9 (IREF)
/PS_GTR/PCIe_Clock/OSC_X1: C324.1, U44.4 (X1/CLK), Y1.1
/PS_GTR/PCIe_Clock/OSC_X2: C325.1, U44.5 (X2), Y1.3
GND: C324.2, C325.2, C326.2, C327.2, C328.2, R222.2, R224.2, R226.2, R228.2, R230.2, U44.2 (S1), U44.7 (GNDX), U44.13 (GNDA), Y1.2 (G), Y1.4 (G); also elsewhere on the board
unnamed: C3.1, R225.2, R226.1
unnamed: C4.1, R223.2, R224.1

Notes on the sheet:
C326: VDDX pin 16 C327: VDDA pin 12 C328: local bulk
100 MHz: S1=0, S0=1 No spread: SS1/SS0 NC (internal pull-ups). Tied to GND = +/-0.25% centre spread, out of PCIe spec (Rev B fault, item 8) Always enabled: OE=1
Y1: X322525MRB4SI / C70593 CL=18pF; 20pF starting load capacitors Keep crystal loop short; ground pads 2/4.
CLK0 -> FPGA: AC-coupled; internal 100-ohm receiver CLK1 -> M.2: DC-coupled HCSL; dedicated output pair
Layout: series/shunt resistors close to U44; shunts BEFORE FPGA AC capacitors. Route independent 100-ohm differential pairs; no output branching. Keep PS_POR_B asserted until clocks are stable (U44 startup allowance: 3ms).

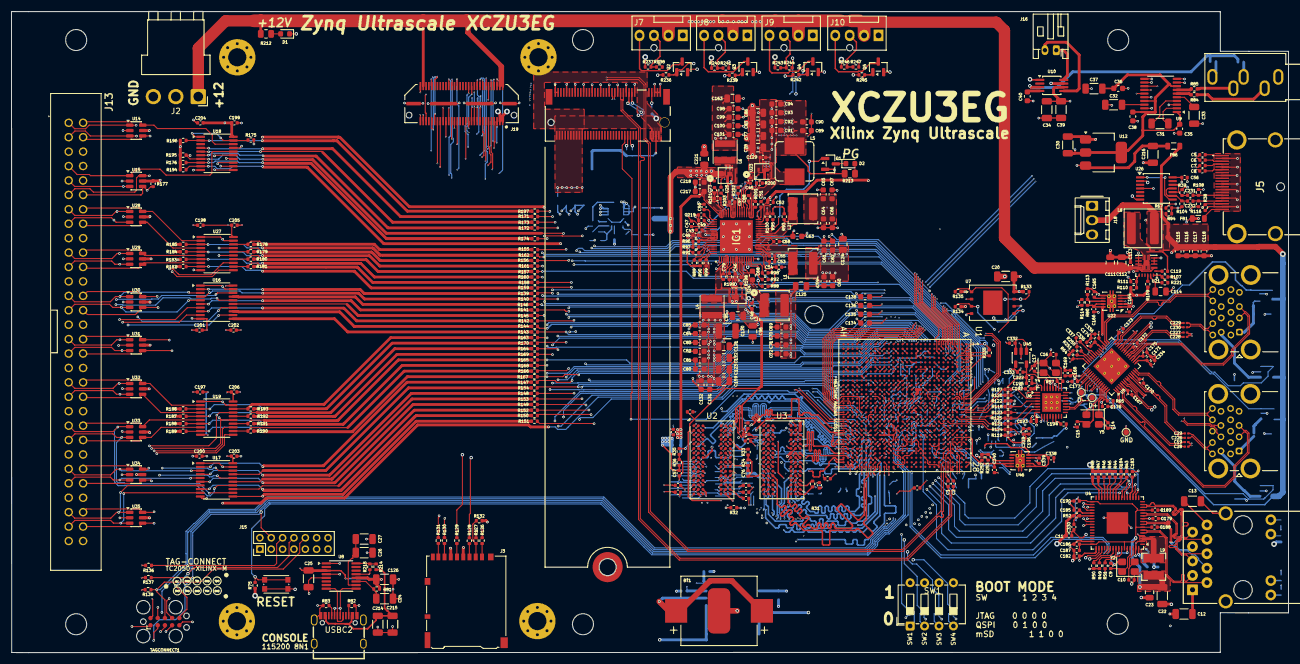
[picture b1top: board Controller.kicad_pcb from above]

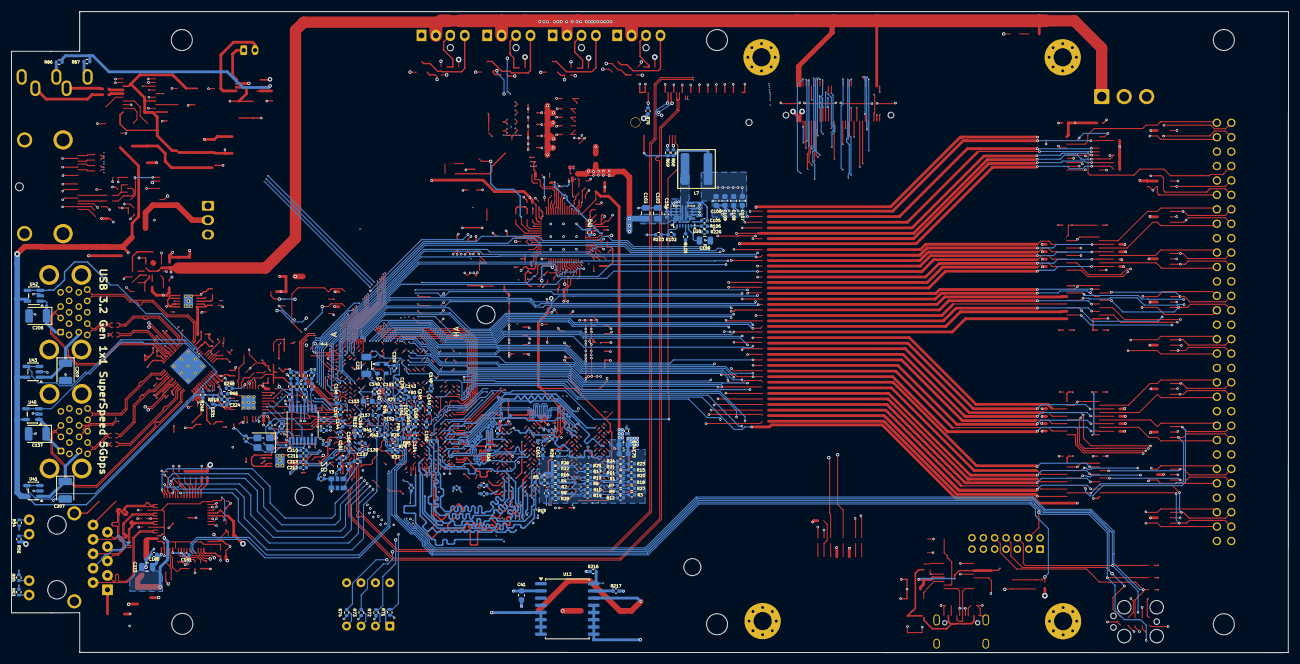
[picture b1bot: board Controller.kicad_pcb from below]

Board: 8 copper layers, 224.9 x 112.9 mm, 613 parts (161 on the bottom side), 571 nets.

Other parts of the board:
RESET1: SW_Push; SW_Push_1P1T_NO_CK_KMR2

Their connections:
/PS_MIO/PS_SRST_B: RESET1.1; also elsewhere on the board
GND: RESET1.2; also elsewhere on the board

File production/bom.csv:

Designator,Footprint,Quantity,Value,LCSC Part #
BT1,BatteryHolder_MYOUNG_MY-1220-03_1x1220,1,CR1220,C964819
"C1, C104, C105, C113, C119, C167, C168, C169, C170, C171, C172, C173, C174, C175, C176, C177, C192, C193, C194, C195, C196, C2, C210, C211, C212, C213, C231, C232, C331, C5, C52, C54, C55, C56, C6, C7, C79, C8, C88, C97",0402,40,0.1uF,C1525
"C10, C16, C17, C9",0402,4,18pF,C1549
"C100, C101, C106, C107, C108, C109, C115, C116, C117, C118, C217, C218, C59, C60, C61, C62, C63, C64, C65, C66, C67, C68, C69, C70, C71, C72, C74, C75, C80, C81, C82, C83, C84, C85, C89, C90, C91, C92, C93, C94, C98, C99",0603,42,22uF,C109448
"C102, C103, C111, C112, C77, C78, C86, C87",0805,8,22uF,C6119899
"C11, C179, C180, C181, C182, C183, C184, C185, C186, C187, C188, C189, C190, C202, C203, C204, C205, C206, C304, C305, C306, C307, C314, C315, C316, C317, C329, C47, C57, C76",0402,30,100nF,C1525
"C110, C114",0805,2,4.7uF,C1779
"C12, C126, C13, C20, C215, C22, C24, C25, C26",1206,9,0.1uF,C24497
C120,1210,1,330uF,C314600
"C121, C122, C123, C124, C125, C159, C163",0805,7,100uF,C141660
"C127, C128, C220, C3, C326, C327, C4",0402,7,10nF,C15195
"C129, C130, C308, C309, C318, C319, C328, C330, C332, C333, C339, C42, C51, C53",0402,14,1uF,C52923
"C131, C132, C133, C134, C135, C136, C138",0603,7,47uF,C140782
"C137, C207, C208, C209",CP_EIA-3528-21_Kemet-B,4,150uF,C212682
"C139, C140, C141, C142, C143, C144, C145, C146, C147, C148, C149, C150, C151, C152, C153, C154, C155, C156, C157, C158, C160, C161, C162, C164, C166, C197, C198, C199, C200, C201, C340, C58, C73",0402,33,10uF,C315248
"C14, C15",0402,2,27pF,C1557
C165,0402,1,47nF,C880605
"C19, C226, C227, C228, C229, C230, C28, C29",0201,8,"100 nF, ±10%, 16 V, X5R",C307380
C21,1206,1,100nF,C24497
"C214, C27",1206,2,4.7uF,C29823
"C216, C37, C39",1206,3,10uF,C13585
"C219, C222, C223, C338, C43, C44, C48, C49, C50",0402,9,4.7uF,C23733
"C221, C95, C96",0805,3,CAP CER 22uF 25V X5R 0805,C6119899
C224,0402,1,2.2uF,C12530
"C23, C233",0805,2,4.7uF,C96454
"C30, C32, C33, C34",1206,4,1uF,C1848
"C300, C301, C302, C303, C310, C312, C313, C320, C321, C322, C323",0402,11,10uF,C307415
C31,1206,1,2.2uF,C50254
"C324, C325",0402,2,20pF,C1554
"C334, C335, C336, C337",0402,4,1nF,C1523
"C35, C36, C38, C40, C41",0603,5,0.1uF,C14663
"C45, C46",0402,2,2.2uF,C170151
"D1, D2",0603,2,LED,C12624
"FB1, FB6",0805,2,FerriteBead,C437406
"FB3, FB4, FB5",0402,3,FerriteBead,C76884
IC1,QFN40P800X800X100-65N-D,1,TPS6508640RSKR,C2659217
"J10, J7, J8, J9",FanPinHeader_1x04_P2.54mm_Vertical,4,Conn_01x04_Pin,C240840
J11,MDT275,1,1-2199119-5,C574849
"J12, J4",USB3_A_Molex_48406-0001_Horizontal_Stacked,2,USB3_A_Stacked,C7501881
J13,09185606324,1,09185606324,C17543813
J15,PinHeader_2x07_P2.00mm_Vertical,1,Conn_02x07_Odd_Even,C240854
J16,JST_PH_S2B-PH-K_1x02_P2.00mm_Horizontal,1,Conn_01x02_Pin,C173752
J17,Jack_3.5mm_CUI_SJ1-3535NG_Horizontal,1,AudioJack3_SwitchTR,C4991610
J18,Molex_KK-254_AE-6410-03A_1x03_P2.54mm_Vertical,1,SZ05S_FAN,C471416
J19,Samtec_QTH-030-03-L-D-A,1,QTH-030-03-L-D-A,C5296114
J2,JST_VH_B3PS-VH_1x03_P3.96mm_Horizontal,1,Conn_01x03_Pin,C131336
J3,microSD_HC_Hirose_DM3AT-SF-PEJM5,1,Micro_SD_Card_Det2,C114218
J5,472720001,1,47272-0001,C587824
J6,RJ45_Hanrun_HR911130A,1,HR911130A,C54408
"L1, L2, L3",L_Chilisin_BWVS00505020,3,0.47µH,C135279
"L4, L6",L_Vishay_IFSC-1515AH_4x4x1.8mm,2,0.47µH,C54321646
L5,L_Bourns_SRP7028A_7.3x6.6mm,1,1µH,C3223644
"L7, L8",L_Bourns_SRP6060FA,2,1.5uH,C5378526
L9,L_Bourns-SRN4018,1,2.2uH,C913207
"Q1, Q2, Q3, Q4, Q5",SOT-23,5,BSS138,C7420339
"R1, R10, R11, R12, R13, R14, R15, R16, R17, R18, R19, R2, R20, R21, R22, R23, R24, R25, R26, R27, R28, R3, R4, R5, R6, R7, R8, R9",0402,28,39.2Ω,C45323
"R100, R101, R103, R105, R109, R111, R113, R114, R115, R175, R178, R179, R180, R181, R182, R183, R184, R185, R186, R187, R188, R189, R190, R191, R192, R193, R194, R195, R196, R214, R215, R216, R217, R235, R236, R237, R239, R240, R242, R243, R245, R246, R248, R253, R32, R33, R34, R35, R36, R43, R44, R45, R46, R47, R49, R50, R52, R55, R56, R64, R68, R69, R70, R75, R76, R77, R78, R79, R81, R88, R89, R90, R91, R92, R93, R95, R96, R97, R98, R99",0402,80,10kΩ,C25744
R102,0402,1,45.3kΩ,C170321
"R104, R39",0402,2,49.9 Ω,C25120
"R106, R107",0402,2,20kΩ,C25765
"R108, R116, R38",0402,3,100kΩ,C25741
R110,0402,1,73.2kΩ,C2998163
R112,0402,1,500Ω,C55205168
"R117, R118, R119, R120, R121, R122, R123, R124, R125, R126, R127, R128, R129, R130, R131",0402,15,30Ω,C138007
"R132, R133, R134, R135, R136, R137, R138, R176, R177, R48, R71, R72, R73, R74",0402,14,4.7kΩ,C25900
"R139, R140, R141, R142, R143, R144, R145, R146, R147, R148, R149, R150, R151, R152, R153, R154, R155, R156, R157, R158, R159, R160, R161, R162, R163, R164, R165, R166, R167, R168, R169, R170, R171, R172, R173, R174, R197, R41",0402,38,22Ω,C25092
"R198, R199, R200, R201, R202, R203",0402,6,2.2Ω,C327251
R212,0805,1,2.2kΩ,C17520
R213,0805,1,470Ω,C17710
"R220, R221",0402,2,120kΩ,C25750
R222,0402,1,475,C137975
"R223, R225, R227, R229",0402,4,33,C25105
"R224, R226, R228, R230, R233, R234",0402,6,49.9,C25120
"R231, R232",0402,2,0,C17168
"R238, R241, R244, R247, R86, R87",0402,6,1kΩ,C11702
R249,0402,1,0Ω,C17168
"R250, R251",0402,2,200kΩ,C25764
R252,0402,1,619Ω,C473032
"R29, R30, R37",0402,3,240Ω,C25094
R31,0402,1,49.9R,C25120
R42,0402,1,1.5kΩ,C25867
R51,0402,1,2.49kΩ,C25884
"R53, R54",0402,2,330Ω,C25104
R57,0402,1,1MΩ,C26083
R65,0402,1,12kΩ,C25752
R66,0402,1,8.06kΩ,C25923
R67,0402,1,2.49 kΩ,C25884
R80,0402,1,4.99kΩ,C25903
"R82, R83",0402,2,5.1kΩ,C25905
"R84, R85",0402,2,470Ω,C25117
R94,0402,1,1.50 kΩ,C25867
RESET1,SW_Push_1P1T_NO_CK_KMR2,1,SW_Push,C72443
SW1,SW_DIP_SPSTx04_Slide_6.7x11.72mm_W7.62mm_P2.54mm_LowProfile,1,SW_DIP_x04,C99418
U1,SFVC784_AMD,1,XCZU3EG-2SFVC784I,C1550463
U10,MSOP-8_3x3mm_P0.65mm,1,PAM8302AASCR,C113367
U12,SOT-223-3_TabPin2,1,AMS1117-3.3,C6186
U13,SOIC-16W_7.5x10.3mm_P1.27mm,1,DS3231M,C37663
"U14, U15, U28, U29, U30, U31, U32, U33, U34, U35",SOT-23-6,10,SRV05-4,C7420376
"U16, U17, U18, U19, U27",SSOP-20_4.4x6.5mm_P0.65mm,5,74LVC244,C6079
"U2, U3",Micron_FBGA-96_7.5x13.5mm_Layout9x16_P0.8mm,2,H5ANAG6NCJR-XNC,C2960662
"U20, U21",Texas_RNN0018A,2,TPS568215RNN,C473367
"U22, U46",VSON-10-1EP_3x3mm_P0.5mm_EP1.65x2.4mm_ThermalVias,2,TPS74801DRC,C105263
"U23, U24, U25",CSD87381P_TEX,3,CSD87381P,C464808
U26,TSSOP-14_4.4x5mm_P0.65mm,1,FIN1019MTC,C903667
U4,QFN-64-1EP_9x9mm_P0.5mm_EP3.8x3.8mm,1,RTL8211EG-VB-CG,C69264
"U40, U41, U42, U43",SOT-23-5,4,AP2171WG-7,C110466
U44,PI6C557-03B_TSSOP16,1,PI6C557-03BLEX,C1540638
U45,SOT-23-5,1,AP2112K-1.8TRG1,C176944
U5,QFN-56-1EP_7x7mm_P0.4mm_EP4.6x4.6mm_ThermalVias,1,USB5744-I/2G,C633621
U6,QFN-32-1EP_5x5mm_P0.5mm_EP3.3x3.3mm_ThermalVias,1,USB3320C-EZK-TR,C132156
U7,WSON-8-1EP_8x6mm_P1.27mm_EP3.4x4.3mm,1,W25Q512JVEIQ TR,C7389628
U8,SSOP-16_3.9x4.9mm_P0.635mm,1,FT230XS,C69082
U9,TSSOP-20_4.4x6.5mm_P0.65mm,1,PCM5102A,C107671
USBC2,USB-C_SMD-TYPE-C-31-M-12,1,TYPE-C-31-M-12,C165948
Y1,YXC_YSX321SL_3225,1,25MHz,C70593
Y2,Crystal_SMD_3225-4Pin_3.2x2.5mm,1,Crystal_GND24,C20617567
Y3,DSC1124_3225,1,DSC1124CI1-027.0000T,C1995498
Y4,Crystal_SMD_3225-4Pin_3.2x2.5mm,1,TX322524M4LBDD2T,C5308006
Y5,Crystal_SMD_3225-4Pin_3.2x2.5mm,1,X1E000021064800,C25832917
Y7,ASDMB_2520,1,ASDMB-33.333MHZ-LC-T,C17497075
